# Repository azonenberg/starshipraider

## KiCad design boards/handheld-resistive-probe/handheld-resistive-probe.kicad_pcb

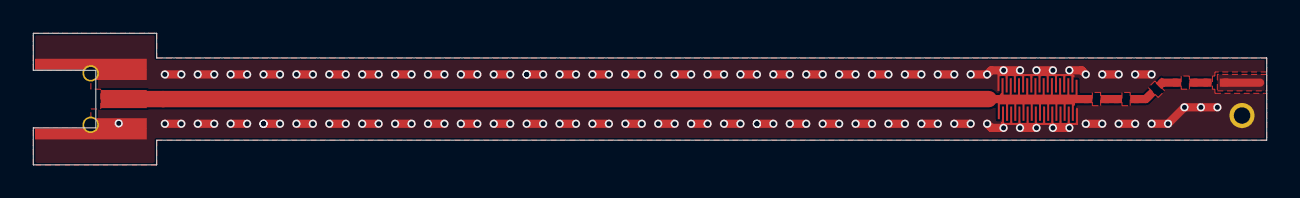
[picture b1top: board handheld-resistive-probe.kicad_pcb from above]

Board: 4 copper layers, 75.0 x 8.0 mm, 9 parts (0 on the bottom side), 6 nets.

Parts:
C1, C2: 500 fF; CAP_MICROSTRIP_0p5PF
J1: Conn_Coaxial; CONN_MMCX_J_P_H_ST_EM1
J2: Conn_01x01; CONN_HEADER_2.54MM_1x1
R1: 50; EIA_0402_RES_NOSILK
R2, R3, R4, R5: 100; EIA_0402_RES_NOSILK

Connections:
/GND: C1.1, C2.1, J1.2, J2.1
/SIGNAL: C1.2, C2.2, J1.1, R1.2
unnamed: R1.1, R2.2
unnamed: R2.1, R3.2
unnamed: R3.1, R4.2
unnamed: R4.1, R5.2

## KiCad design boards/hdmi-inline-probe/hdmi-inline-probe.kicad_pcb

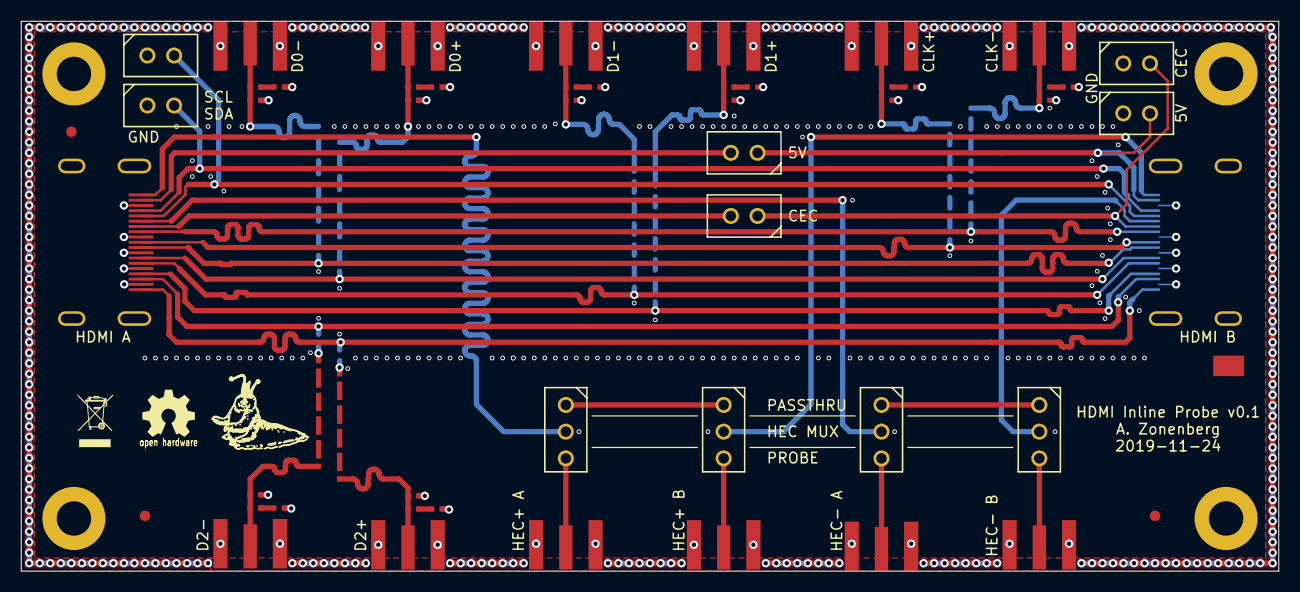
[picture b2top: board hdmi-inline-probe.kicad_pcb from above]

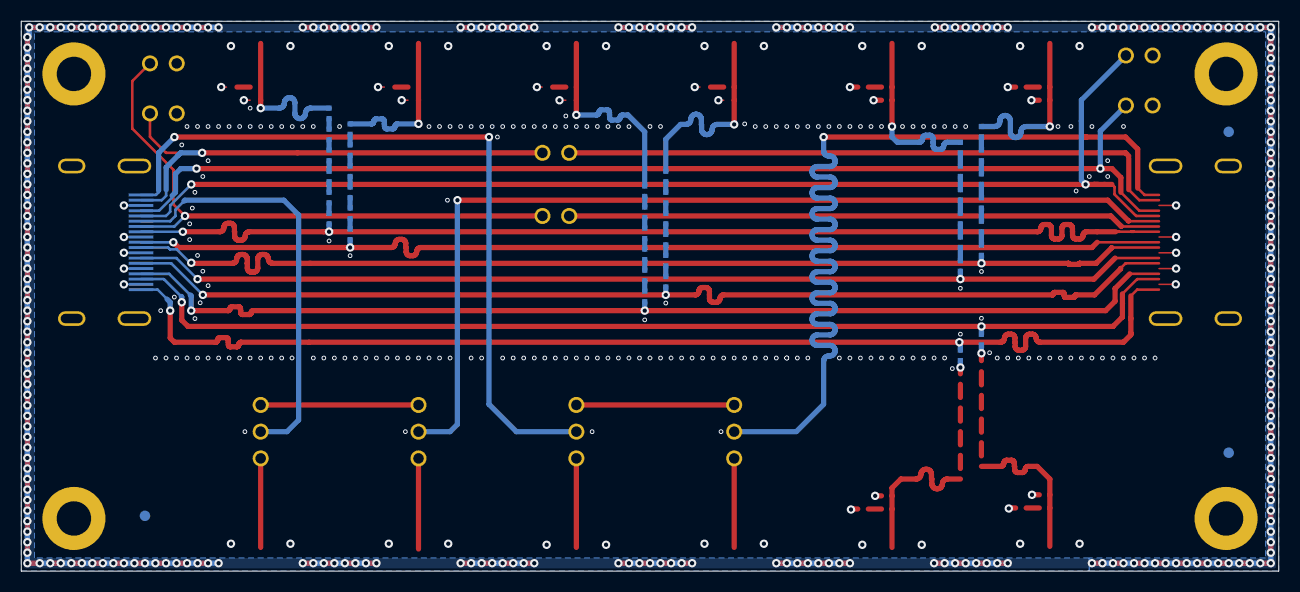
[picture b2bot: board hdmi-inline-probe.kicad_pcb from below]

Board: 4 copper layers, 119.5 x 52.2 mm, 102 parts (42 on the bottom side), 81 nets.

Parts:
C1, C2, C3, C4, C5, C6, C7, C8: 0.1 uF; EIA_0402_CAP_NOSILK
C9, C10, C11, C12, C13, C14, C15, C16, C17, C18, C19, C20, C21, C22, C23, C24: DNP; EIA_0402_CAP_NOSILK
FIDUCIAL_1MM, FIDUCIAL_1MM#2, FIDUCIAL_1MM#3, FIDUCIAL_1MM#4, FIDUCIAL_1MM#5, FIDUCIAL_1MM#6: VAL**; FIDUCIAL_1MM
J1, J2, J6, J7: Conn_01x03; CONN_HEADER_2.54MM_1x3
J3, J4: Conn_01x02; CONN_HEADER_2.54MM_1x2
J5: HDMI_A_OUTPUT; CONN_HDMI_SAMTEC_HDMR_19_01_S_SM
J8: HDMI_A_INPUT; CONN_HDMI_SAMTEC_HDMR_19_01_S_SM
J9, J10, J11, J12, J13, J14, J15, J16, J17, J18, J19, J20: SMA; CONN_SMA_EDGE_SAMTEC_SMA_J_P_H_ST_EM1
R1, R2, R3, R4, R5, R6, R7, R8, R9, R10, R11, R12, R13, R14, R15, R16, R17, R18, R19, R20, R21, R22, R23, R24, R25, R26, R27, R28, R29, R30, R31, R32, R33, R34, R35, R36, R37, R38, R39, R40: 200; EIA_0402_RES_NOSILK
R41, R42, R43, R44, R45, R46, R47, R48: DNP; EIA_0402_RES_NOSILK
TP1, TP2, TP3, TP4: Conn_01x02; CONN_HEADER_2.54MM_1x2

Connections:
/5V_IN: J4.1, J8.18, TP4.2
/5V_OUT: J4.2, J5.18
/CEC_IN: J3.1, J8.13, TP3.2
/CEC_OUT: J3.2, J5.13
/GND: C9.2, C10.2, C11.2, C12.2, C13.2, C14.2, C15.2, C16.2, J5.2, J5.5, J5.8, J5.11, J5.17, J5.SHLD, J8.2, J8.5, J8.8, J8.11, J8.17, J8.SHLD, J9.2, J10.2, J11.2, J12.2, J13.2, J14.2, J15.2, J16.2, J17.2, J18.2, J19.2, J20.2, R41.2, R42.2, R43.2, R44.2, R45.2, R46.2, R47.2, R48.2, TP1.1, TP2.1, TP3.1, TP4.1
/HEC_IN_N: J2.2, J8.14
/HEC_IN_P: J1.2, J8.19
/HEC_OUT_N: J5.14, J7.2
/HEC_OUT_P: J5.19, J6.2
/HEC_PASSTHRU_N: J2.1, J7.1
/HEC_PASSTHRU_P: J1.1, J6.1
/HEC_PROBE_IN_N: J2.3, J18.1
/HEC_PROBE_IN_P: J1.3, J17.1
/HEC_PROBE_OUT_N: J7.3, J20.1
/HEC_PROBE_OUT_P: J6.3, J19.1
/I2C_SCL: J5.15, J8.15, TP2.2
/I2C_SDA: J5.16, J8.16, TP1.2
/PROBE_CLK_N: C10.1, C18.1, J10.1, R34.1
/PROBE_CLK_P: C9.1, C17.1, J9.1, R33.1
/PROBE_D0_N: C12.1, C20.1, J12.1, R36.1
/PROBE_D0_P: C11.1, C19.1, J11.1, R35.1
/PROBE_D1_N: C14.1, C22.1, J14.1, R38.1
/PROBE_D1_P: C13.1, C21.1, J13.1, R37.1
/PROBE_D2_N: C16.1, C24.1, J16.1, R40.1
/PROBE_D2_P: C15.1, C23.1, J15.1, R39.1
/TMDS_CLK_N: C2.2, J5.12, J8.12
/TMDS_CLK_P: C1.2, J5.10, J8.10
/TMDS_D0_N: C4.2, J5.9, J8.9
/TMDS_D0_P: C3.2, J5.7, J8.7
/TMDS_D1_N: C6.2, J5.6, J8.6
/TMDS_D1_P: C5.2, J5.4, J8.4
/TMDS_D2_N: C8.2, J5.3, J8.3
/TMDS_D2_P: C7.2, J5.1, J8.1
unnamed: C1.1, R1.2
unnamed: C2.1, R2.2
unnamed: C3.1, R3.2
unnamed: C4.1, R4.2
unnamed: C5.1, R5.2
unnamed: C6.1, R6.2
unnamed: C7.1, R7.2
unnamed: C8.1, R8.2
unnamed: C17.2, R41.1
unnamed: C18.2, R42.1
unnamed: C19.2, R43.1
unnamed: C20.2, R44.1
unnamed: C21.2, R45.1
unnamed: C22.2, R46.1
unnamed: C23.2, R47.1
unnamed: C24.2, R48.1
unnamed: R1.1, R9.2
unnamed: R10.1, R18.2
unnamed: R2.1, R10.2
unnamed: R11.1, R19.2
unnamed: R3.1, R11.2
unnamed: R12.1, R20.2
unnamed: R4.1, R12.2
unnamed: R13.1, R21.2
unnamed: R5.1, R13.2
unnamed: R14.1, R22.2
unnamed: R6.1, R14.2
unnamed: R15.1, R23.2
unnamed: R7.1, R15.2
unnamed: R16.1, R24.2
unnamed: R8.1, R16.2
unnamed: R17.1, R25.2
unnamed: R9.1, R17.2
unnamed: R18.1, R26.2
unnamed: R19.1, R27.2
unnamed: R20.1, R28.2
unnamed: R21.1, R29.2
unnamed: R22.1, R30.2
unnamed: R23.1, R31.2
unnamed: R24.1, R32.2
unnamed: R25.1, R33.2
unnamed: R26.1, R34.2
unnamed: R27.1, R35.2
unnamed: R28.1, R36.2
unnamed: R29.1, R37.2
unnamed: R30.1, R38.2
unnamed: R31.1, R39.2
unnamed: R32.1, R40.2

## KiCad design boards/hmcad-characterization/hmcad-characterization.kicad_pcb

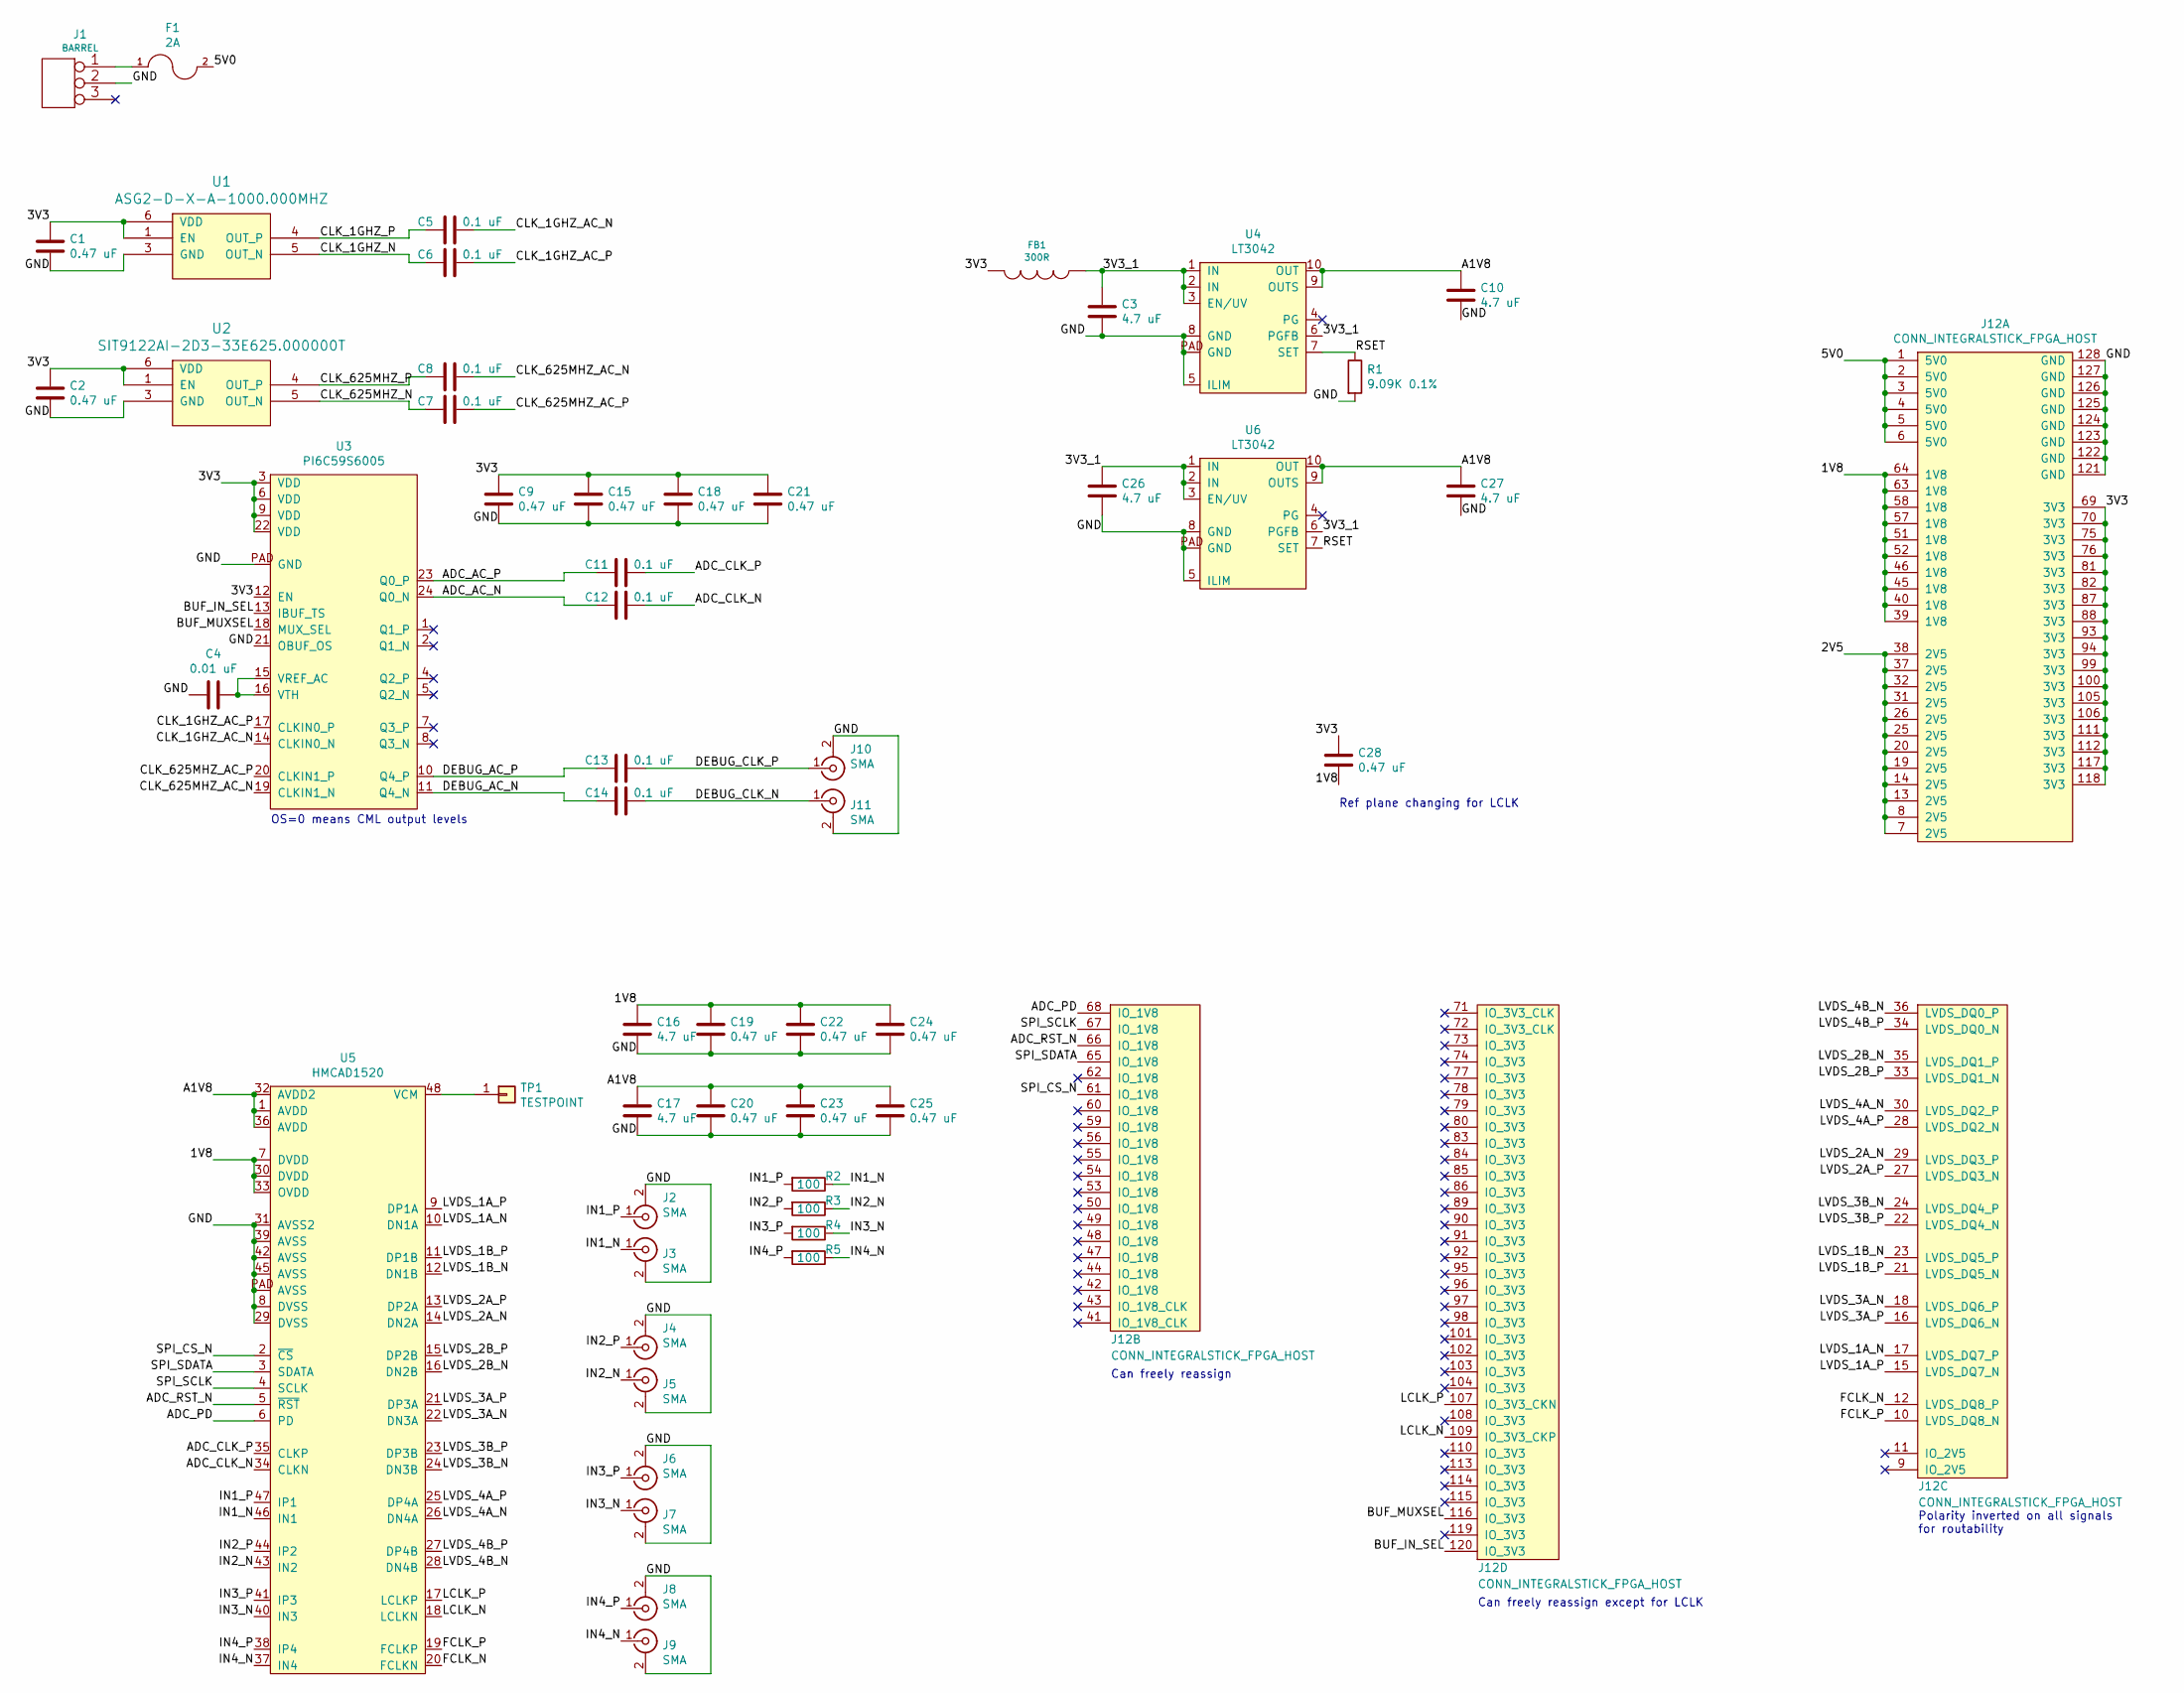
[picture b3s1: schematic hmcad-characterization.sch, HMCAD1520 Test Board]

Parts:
C1, C2, C9, C15, C18, C19, C20, C21, C22, C23, C24, C25, C28: 0.47 uF; EIA_0402_CAP_NOSILK
C3, C10, C16, C17, C26, C27: 4.7 uF; EIA_0603_CAP_NOSILK
C4: 0.01 uF; EIA_0402_CAP_NOSILK
C5, C6, C7, C8, C11, C12, C13, C14: 0.1 uF; EIA_0402_CAP_NOSILK
F1: 2A; EIA_0603_INDUCTOR_NOSILK
FB1: 300R; EIA_0603_INDUCTOR_NOSILK
J1: BARREL; CONN_CUI_PJ-058BH_HIPWR_BARREL_NOSLOT
J2, J3, J4, J5, J6, J7, J8, J9, J10, J11: SMA; CONN_SMA_EDGE_SAMTEC_SMA_J_P_H_ST_EM1
J12: CONN_INTEGRALSTICK_FPGA_HOST; CONN_SAMTEC_QSH-060-01-L-D-A
R1: 9.09K 0.1%; EIA_0402_RES_NOSILK
R2, R3, R4, R5: 100; EIA_0402_RES_NOSILK
TP1: TESTPOINT; TESTPOINT_SMT_0.5MM
U1: ASG2-D-X-A-1000.000MHZ; OSCILLATOR_LVDS_2.5x2.0
U2: SIT9122AI-2D3-33E625.000000T; OSCILLATOR_LVDS_7.0x5.0
U3: PI6C59S6005; QFN_24_0.5MM_4x4MM
U4, U6: LT3042; DFN_10_0.5MM_3x3MM
U5: HMCAD1520; QFN_48_0.5MM_7x7MM

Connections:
/1V8: C16.2, C19.2, C22.2, C24.2, C28.1, J12.39 (1V8), J12.40 (1V8), J12.45 (1V8), J12.46 (1V8), J12.51 (1V8), J12.52 (1V8), J12.57 (1V8), J12.58 (1V8), J12.63 (1V8), J12.64 (1V8), U5.7 (DVDD), U5.30 (DVDD), U5.33 (OVDD); also elsewhere on the board
/2V5: J12.7 (2V5), J12.8 (2V5), J12.13 (2V5), J12.14 (2V5), J12.19 (2V5), J12.20 (2V5), J12.25 (2V5), J12.26 (2V5), J12.31 (2V5), J12.32 (2V5), J12.37 (2V5), J12.38 (2V5); also elsewhere on the board
/3V3: C1.1, C2.1, C9.1, C15.1, C18.1, C21.1, C28.2, FB1.2, J12.69 (3V3), J12.70 (3V3), J12.75 (3V3), J12.76 (3V3), J12.81 (3V3), J12.82 (3V3), J12.87 (3V3), J12.88 (3V3), J12.93 (3V3), J12.94 (3V3), J12.99 (3V3), J12.100 (3V3), J12.105 (3V3), J12.106 (3V3), J12.111 (3V3), J12.112 (3V3), J12.117 (3V3), J12.118 (3V3), U1.1 (EN), U1.6 (VDD), U2.1 (EN), U2.6 (VDD), U3.3 (VDD), U3.6 (VDD), U3.9 (VDD), U3.12 (EN), U3.22 (VDD)
/3V3_1: C3.2, C26.2, FB1.1, U4.1 (IN), U4.2 (IN), U4.3 (EN/UV), U4.6 (PGFB), U6.1 (IN), U6.2 (IN), U6.3 (EN/UV), U6.6 (PGFB)
/5V0: F1.2, J12.1 (5V0), J12.2 (5V0), J12.3 (5V0), J12.4 (5V0), J12.5 (5V0), J12.6 (5V0)
/A1V8: C10.2, C17.2, C20.2, C23.2, C25.2, C27.2, U4.9 (OUTS), U4.10 (OUT), U5.1 (AVDD), U5.32 (AVDD2), U5.36 (AVDD), U6.9 (OUTS), U6.10 (OUT)
/ADC_AC_N: C12.2, U3.24 (Q0_N)
/ADC_AC_P: C11.2, U3.23 (Q0_P)
/ADC_CLK_N: C12.1, U5.34 (CLKN)
/ADC_CLK_P: C11.1, U5.35 (CLKP)
/ADC_PD: J12.68 (IO_1V8), U5.6 (PD)
/ADC_RST_N: J12.66 (IO_1V8), U5.5 (~RST)
/BUF_IN_SEL: J12.120 (IO_3V3), U3.13 (IBUF_TS)
/BUF_MUXSEL: J12.116 (IO_3V3), U3.18 (MUX_SEL)
/CLK_1GHZ_AC_N: C5.1, U3.14 (CLKIN0_N)
/CLK_1GHZ_AC_P: C6.1, U3.17 (CLKIN0_P)
/CLK_1GHZ_N: C6.2, U1.5 (OUT_N)
/CLK_1GHZ_P: C5.2, U1.4 (OUT_P)
/CLK_625MHZ_AC_N: C8.1, U3.19 (CLKIN1_N)
/CLK_625MHZ_AC_P: C7.1, U3.20 (CLKIN1_P)
/CLK_625MHZ_N: C7.2, U2.5 (OUT_N)
/CLK_625MHZ_P: C8.2, U2.4 (OUT_P)
/DEBUG_AC_N: C14.2, U3.11 (Q4_N)
/DEBUG_AC_P: C13.2, U3.10 (Q4_P)
/DEBUG_CLK_N: C14.1, J11.1 (In)
/DEBUG_CLK_P: C13.1, J10.1 (In)
/FCLK_N: J12.12 (LVDS_DQ8_P), U5.20 (FCLKN)
/FCLK_P: J12.10 (LVDS_DQ8_N), U5.19 (FCLKP)
/GND: C1.2, C2.2, C3.1, C4.2, C9.2, C10.1, C15.2, C16.1, C17.1, C18.2, C19.1, C20.1, C21.2, C22.1, C23.1, C24.1, C25.1, C26.1, C27.1, J1.2 (PM), J2.2 (Ext), J3.2 (Ext), J4.2 (Ext), J5.2 (Ext), J6.2 (Ext), J7.2 (Ext), J8.2 (Ext), J9.2 (Ext), J10.2 (Ext), J11.2 (Ext), J12.121 (GND), J12.122 (GND), J12.123 (GND), J12.124 (GND), J12.125 (GND), J12.126 (GND), J12.127 (GND), J12.128 (GND), R1.2, U1.3 (GND), U2.3 (GND), U3.21 (OBUF_OS), U3.PAD (GND), U4.5 (ILIM), U4.8 (GND), U4.PAD (GND), U5.8 (DVSS), U5.29 (DVSS), U5.31 (AVSS2), U5.39 (AVSS), U5.42 (AVSS), U5.45 (AVSS), U5.PAD (AVSS), U6.5 (ILIM), U6.8 (GND), U6.PAD (GND)
/IN1_N: J3.1 (In), R2.1, U5.46 (IN1)
/IN1_P: J2.1 (In), R2.2, U5.47 (IP1)
/IN2_N: J5.1 (In), R3.1, U5.43 (IN2)
/IN2_P: J4.1 (In), R3.2, U5.44 (IP2)
/IN3_N: J7.1 (In), R4.1, U5.40 (IN3)
/IN3_P: J6.1 (In), R4.2, U5.41 (IP3)
/IN4_N: J9.1 (In), R5.1, U5.37 (IN4)
/IN4_P: J8.1 (In), R5.2, U5.38 (IP4)
/LCLK_N: J12.109 (IO_3V3_CKP), U5.18 (LCLKN)
/LCLK_P: J12.107 (IO_3V3_CKN), U5.17 (LCLKP)
/LVDS_1A_N: J12.17 (LVDS_DQ7_P), U5.10 (DN1A)
/LVDS_1A_P: J12.15 (LVDS_DQ7_N), U5.9 (DP1A)
/LVDS_1B_N: J12.23 (LVDS_DQ5_P), U5.12 (DN1B)
/LVDS_1B_P: J12.21 (LVDS_DQ5_N), U5.11 (DP1B)
/LVDS_2A_N: J12.29 (LVDS_DQ3_P), U5.14 (DN2A)
/LVDS_2A_P: J12.27 (LVDS_DQ3_N), U5.13 (DP2A)
/LVDS_2B_N: J12.35 (LVDS_DQ1_P), U5.16 (DN2B)
/LVDS_2B_P: J12.33 (LVDS_DQ1_N), U5.15 (DP2B)
/LVDS_3A_N: J12.18 (LVDS_DQ6_P), U5.22 (DN3A)
/LVDS_3A_P: J12.16 (LVDS_DQ6_N), U5.21 (DP3A)
/LVDS_3B_N: J12.24 (LVDS_DQ4_P), U5.24 (DN3B)
/LVDS_3B_P: J12.22 (LVDS_DQ4_N), U5.23 (DP3B)
/LVDS_4A_N: J12.30 (LVDS_DQ2_P), U5.26 (DN4A)
/LVDS_4A_P: J12.28 (LVDS_DQ2_N), U5.25 (DP4A)
/LVDS_4B_N: J12.36 (LVDS_DQ0_P), U5.28 (DN4B)
/LVDS_4B_P: J12.34 (LVDS_DQ0_N), U5.27 (DP4B)
/RSET: R1.1, U4.7 (SET), U6.7 (SET)
/SPI_CS_N: J12.61 (IO_1V8), U5.2 (~CS)
/SPI_SCLK: J12.67 (IO_1V8), U5.4 (SCLK)
/SPI_SDATA: J12.65 (IO_1V8), U5.3 (SDATA)
unnamed: C4.1, U3.15 (VREF_AC), U3.16 (VTH)
unnamed: F1.1, J1.1
unnamed: TP1.1, U5.48 (VCM)

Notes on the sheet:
OS=0 means CML output levels
Can freely reassign
Can freely reassign except for LCLK
Polarity inverted on all signals for routability
Ref plane changing for LCLK

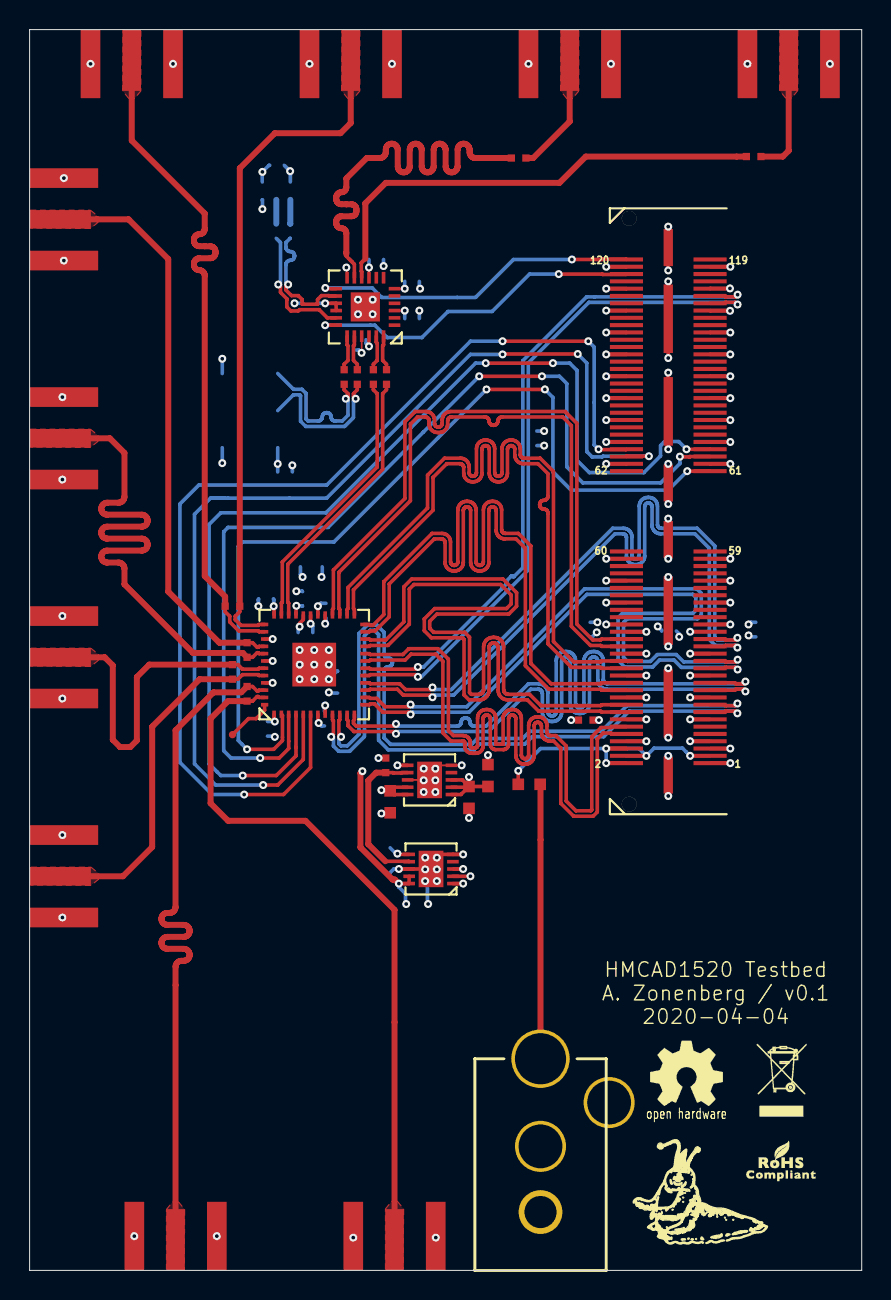
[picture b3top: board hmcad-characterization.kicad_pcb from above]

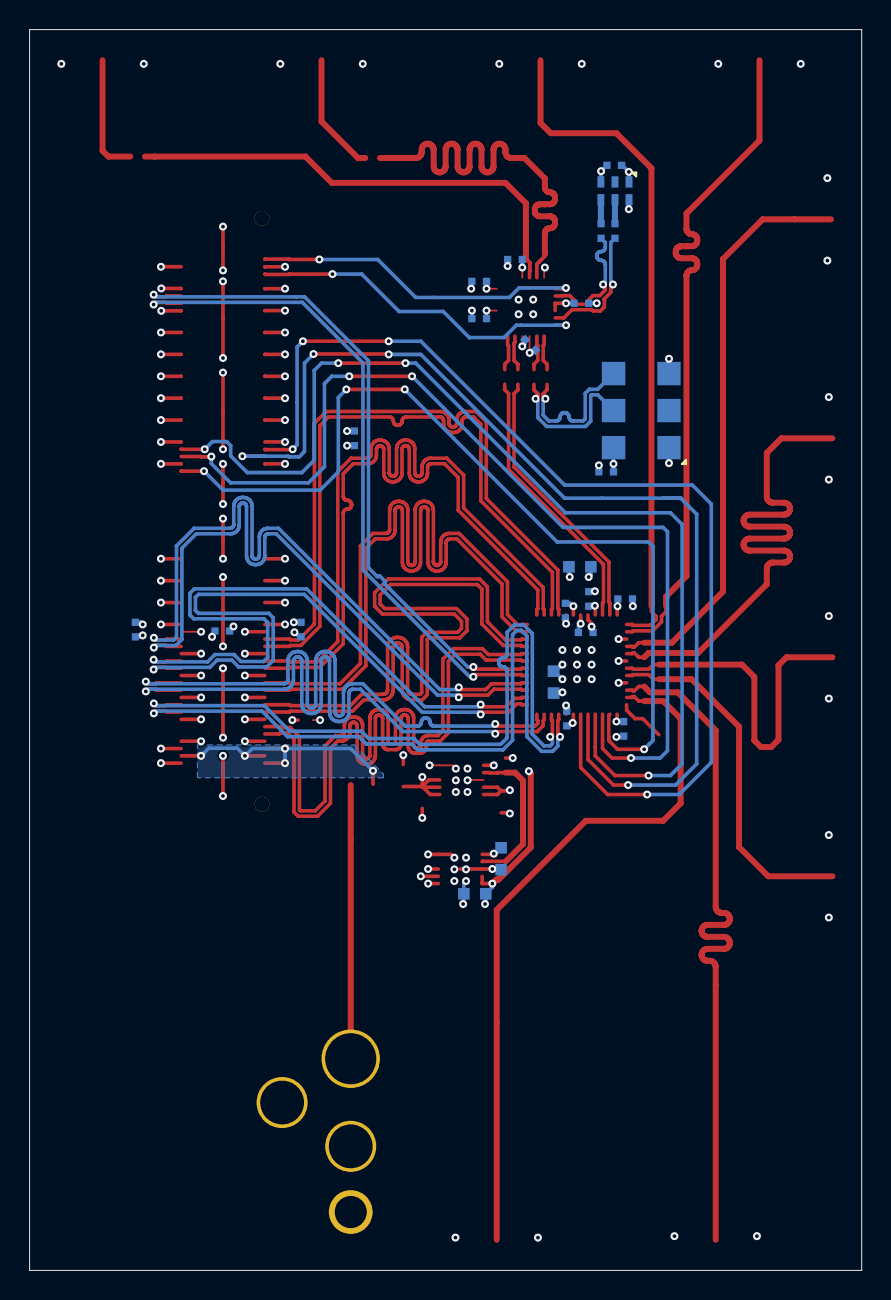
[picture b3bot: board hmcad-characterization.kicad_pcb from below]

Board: 4 copper layers, 57.0 x 85.0 mm, 58 parts (25 on the bottom side), 62 nets.

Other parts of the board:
C29, C30, C31, C32: 0.47 uF; EIA_0402_CAP_NOSILK

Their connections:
/1V8: C29.1, C30.1, C31.1, C32.1; also elsewhere on the board
/2V5: C29.2, C30.2, C31.2, C32.2; also elsewhere on the board

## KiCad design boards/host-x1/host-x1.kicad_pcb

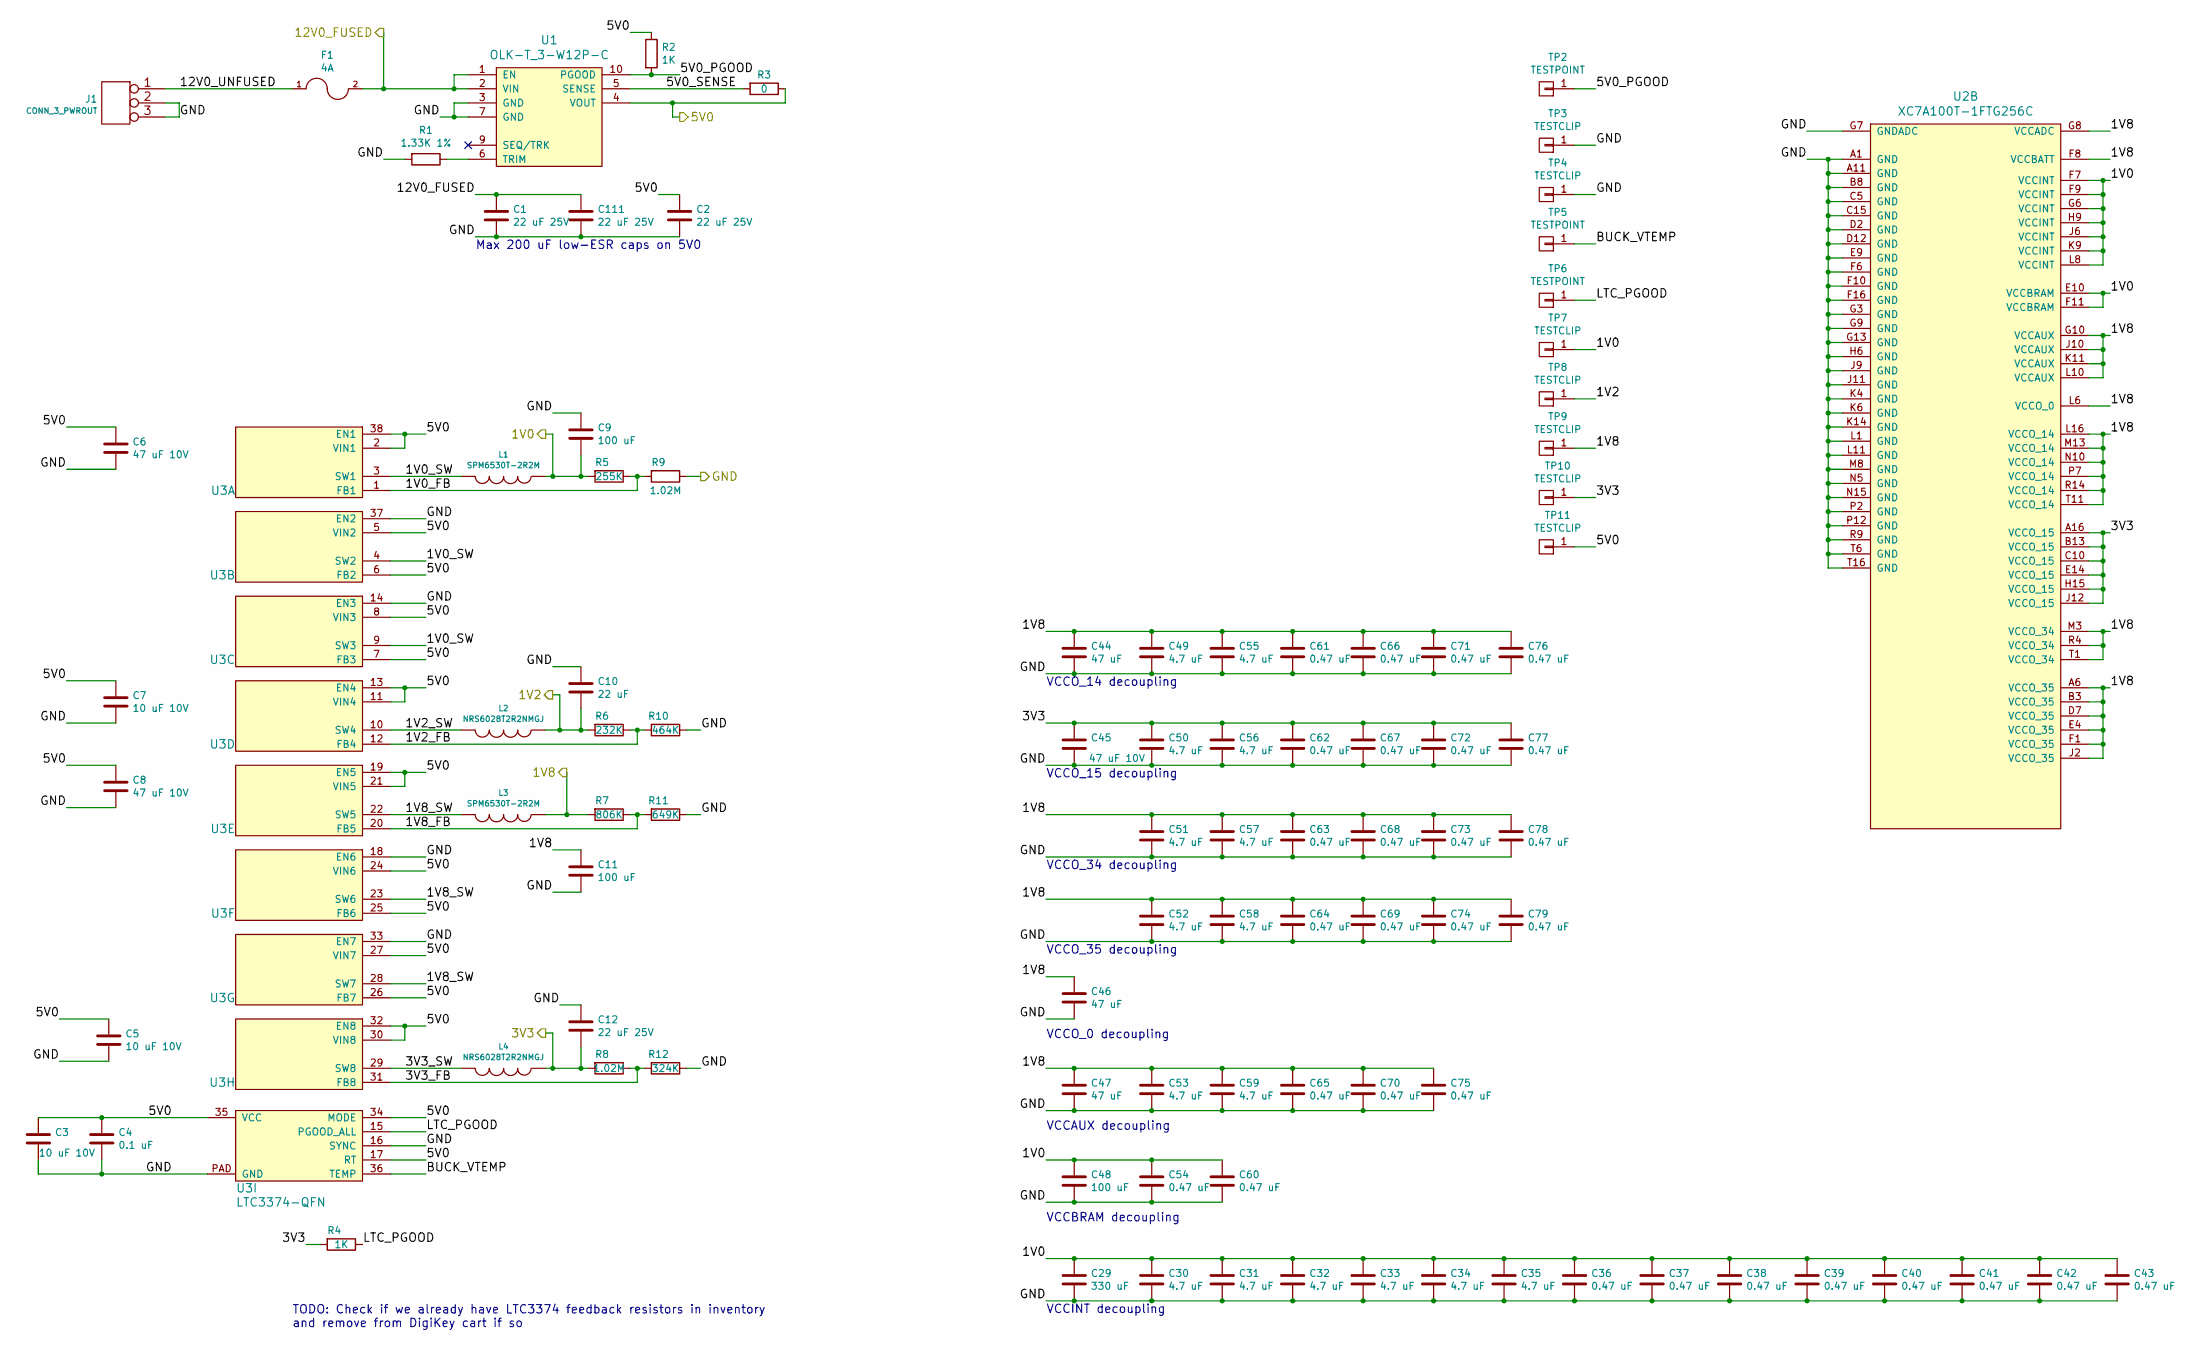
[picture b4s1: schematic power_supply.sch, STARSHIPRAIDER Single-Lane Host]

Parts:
C1, C2, C12, C111: 22 uF 25V; EIA_1210_CAP_NOSILK
C3, C5, C7: 10 uF 10V; EIA_1206_CAP_NOSILK
C4: 0.1 uF; EIA_0402_CAP_NOSILK
C6, C8, C45: 47 uF 10V; EIA_1210_CAP_NOSILK
C9, C11, C48: 100 uF; EIA_1210_CAP_NOSILK
C10: 22 uF; EIA_0805_CAP_NOSILK
C29: 330 uF; EIA_1210_CAP_NOSILK
C30, C31, C32, C33, C34, C35, C49, C50, C51, C52, C53, C55, C56, C57, C58, C59: 4.7 uF; EIA_0603_CAP_NOSILK
C36, C37, C38, C39, C40, C41, C42, C43, C54, C60, C61, C62, C63, C64, C65, C66, C67, C68, C69, C70, C71, C72, C73, C74, C75, C76, C77, C78, C79: 0.47 uF; EIA_0402_CAP_NOSILK
C44, C46, C47: 47 uF; EIA_0805_CAP_NOSILK
F1: 4A; EIA_0402_RES_NOSILK
J1: CONN_3_PWROUT; CONN_CUI_PJ-058BH_HIPWR_BARREL_NOSLOT
L1, L3: SPM6530T-2R2M; INDUCTOR_TDK_SPM6530
L2, L4: NRS6028T2R2NMGJ; INDUCTOR_YUDEN_NR6028
R1: 1.33K 1%; EIA_0402_RES_NOSILK
R2, R4: 1K; EIA_0402_RES_NOSILK
R3: 0; EIA_0402_RES_NOSILK
R5: 255K; EIA_0402_RES_NOSILK
R6: 232K; EIA_0402_RES_NOSILK
R7: 806K; EIA_0402_RES_NOSILK
R8, R9: 1.02M; EIA_0402_RES_NOSILK
R10: 464K; EIA_0402_RES_NOSILK
R11: 649K; EIA_0402_RES_NOSILK
R12: 324K; EIA_0402_RES_NOSILK
TP2, TP5, TP6: TESTPOINT; TESTPOINT_SMT_0.5MM
TP3, TP4, TP7, TP8, TP9, TP10, TP11: TESTCLIP; TESTPOINT_SMT_KEYSTONE_5016
U1: OLK-T_3-W12P-C; MODULE_MURATA_OKL-T3-W12
U2: XC7A100T-1FTG256C; BGA_256_17x17_FULLARRAY_1MM
U3: LTC3374-QFN; QFN_38_0.5MM_5x7MM

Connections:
/1V0: C9.2, C29.1, C30.1, C31.1, C32.1, C33.1, C34.1, C35.1, C36.1, C37.1, C38.1, C39.1, C40.1, C41.1, C42.1, C43.1, C48.1, C54.1, C60.1, L1.1, R5.2, TP7.1, U2.E10 (VCCBRAM), U2.F7 (VCCINT), U2.F9 (VCCINT), U2.F11 (VCCBRAM), U2.G6 (VCCINT), U2.H9 (VCCINT), U2.J6 (VCCINT), U2.K9 (VCCINT), U2.L8 (VCCINT)
/1V2: C10.2, L2.1, R6.2, TP8.1; also elsewhere on the board
/1V8: C11.1, C44.1, C46.1, C47.1, C49.1, C51.1, C52.1, C53.1, C55.1, C57.1, C58.1, C59.1, C61.1, C63.1, C64.1, C65.1, C66.1, C68.1, C69.1, C70.1, C71.1, C73.1, C74.1, C75.1, C76.1, C78.1, C79.1, L3.1, R7.2, TP9.1, U2.A6 (VCCO_35), U2.B3 (VCCO_35), U2.D7 (VCCO_35), U2.E4 (VCCO_35), U2.F1 (VCCO_35), U2.F8 (VCCBATT), U2.G8 (VCCADC), U2.G10 (VCCAUX), U2.J2 (VCCO_35), U2.J10 (VCCAUX), U2.K11 (VCCAUX), U2.L6 (VCCO_0), U2.L10 (VCCAUX), U2.L16 (VCCO_14), U2.M3 (VCCO_34), U2.M13 (VCCO_14), U2.N10 (VCCO_14), U2.P7 (VCCO_14), U2.R4 (VCCO_34), U2.R14 (VCCO_14), U2.T1 (VCCO_34), U2.T11 (VCCO_14); also elsewhere on the board
/3V3: C12.2, C45.1, C50.1, C56.1, C62.1, C67.1, C72.1, C77.1, L4.1, R4.2, R8.2, TP10.1, U2.A16 (VCCO_15), U2.B13 (VCCO_15), U2.C10 (VCCO_15), U2.E14 (VCCO_15), U2.H15 (VCCO_15), U2.J12 (VCCO_15); also elsewhere on the board
/5V0: C2.1, C3.1, C4.1, C5.1, C6.1, C7.1, C8.1, R2.1, R3.1, TP11.1, U1.4 (VOUT), U3.2 (VIN1), U3.5 (VIN2), U3.6 (FB2), U3.7 (FB3), U3.8 (VIN3), U3.11 (VIN4), U3.13 (EN4), U3.17 (RT), U3.19 (EN5), U3.21 (VIN5), U3.24 (VIN6), U3.25 (FB6), U3.26 (FB7), U3.27 (VIN7), U3.30 (VIN8), U3.32 (EN8), U3.34 (MODE), U3.35 (VCC), U3.38 (EN1); also elsewhere on the board
/12V0_FUSED: C1.1, C111.1, F1.2, U1.1 (EN), U1.2 (VIN); also elsewhere on the board
/GND: C1.2, C2.2, C3.2, C4.2, C5.2, C6.2, C7.2, C8.2, C9.1, C10.1, C11.2, C12.1, C29.2, C30.2, C31.2, C32.2, C33.2, C34.2, C35.2, C36.2, C37.2, C38.2, C39.2, C40.2, C41.2, C42.2, C43.2, C44.2, C45.2, C46.2, C47.2, C48.2, C49.2, C50.2, C51.2, C52.2, C53.2, C54.2, C55.2, C56.2, C57.2, C58.2, C59.2, C60.2, C61.2, C62.2, C63.2, C64.2, C65.2, C66.2, C67.2, C68.2, C69.2, C70.2, C71.2, C72.2, C73.2, C74.2, C75.2, C76.2, C77.2, C78.2, C79.2, C111.2, J1.2 (PM), J1.3, R1.2, R9.1, R10.1, R11.1, R12.1, TP3.1, TP4.1, U1.3 (GND), U1.7 (GND), U2.A1 (GND), U2.A11 (GND), U2.B8 (GND), U2.C5 (GND), U2.C15 (GND), U2.D2 (GND), U2.D12 (GND), U2.E9 (GND), U2.F6 (GND), U2.F10 (GND), U2.F16 (GND), U2.G3 (GND), U2.G7 (GNDADC), U2.G9 (GND), U2.G13 (GND), U2.H6 (GND), U2.J9 (GND), U2.J11 (GND), U2.K4 (GND), U2.K6 (GND), U2.K14 (GND), U2.L1 (GND), U2.L11 (GND), U2.M8 (GND), U2.N5 (GND), U2.N15 (GND), U2.P2 (GND), U2.P12 (GND), U2.R9 (GND), U2.T6 (GND), U2.T16 (GND), U3.14 (EN3), U3.16 (SYNC), U3.18 (EN6), U3.33 (EN7), U3.37 (EN2), U3.PAD (GND); also elsewhere on the board
/Power Supply/1V0_FB: R5.1, R9.2, U3.1 (FB1)
/Power Supply/1V0_SW: L1.2, U3.3 (SW1), U3.4 (SW2), U3.9 (SW3)
/Power Supply/1V2_FB: R6.1, R10.2, U3.12 (FB4)
/Power Supply/1V2_SW: L2.2, U3.10 (SW4)
/Power Supply/1V8_FB: R7.1, R11.2, U3.20 (FB5)
/Power Supply/1V8_SW: L3.2, U3.22 (SW5), U3.23 (SW6), U3.28 (SW7)
/Power Supply/3V3_FB: R8.1, R12.2, U3.31 (FB8)
/Power Supply/3V3_SW: L4.2, U3.29 (SW8)
/Power Supply/5V0_PGOOD: R2.2, TP2.1, U1.10 (PGOOD)
/Power Supply/5V0_SENSE: R3.2, U1.5 (SENSE)
/Power Supply/12V0_UNFUSED: F1.1, J1.1
/Power Supply/BUCK_VTEMP: TP5.1, U3.36 (TEMP)
/Power Supply/LTC_PGOOD: R4.1, TP6.1, U3.15 (PGOOD_ALL)
unnamed: R1.1, U1.6 (TRIM)

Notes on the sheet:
Max 200 uF low-ESR caps on 5V0
VCCINT decoupling
VCCBRAM decoupling
VCCAUX decoupling
VCCO_0 decoupling
VCCO_35 decoupling
VCCO_34 decoupling
VCCO_15 decoupling
VCCO_14 decoupling
TODO: Check if we already have LTC3374 feedback resistors in inventory and remove from DigiKey cart if so
